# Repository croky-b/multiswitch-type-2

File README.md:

# multiswitch-type-2

/*================= TDB USM  ========================
   original code from bricodx : http://www.bricodx.fr/articles/9-arduino/16-commande-multifonctions/
   modified by croky_b for the Boat_Engine_system_MAXI
======================================================*/

not tested with 16 entry 

R1 180 ohm
R2 180 ohm

R3 2.2k ( for fotaba FC16)
R4 2.2k ( for futaba FC16)

R5 82k for old futaba F14 7 kanal ( if not used use SJ1)

OPTO PC817

Pinheader 
https://www.ebay.fr/itm/191203299649

switch
https://www.ebay.fr/itm/352543390865?hash=item5215393c91:g:xXUAAOSwkSde9JuG

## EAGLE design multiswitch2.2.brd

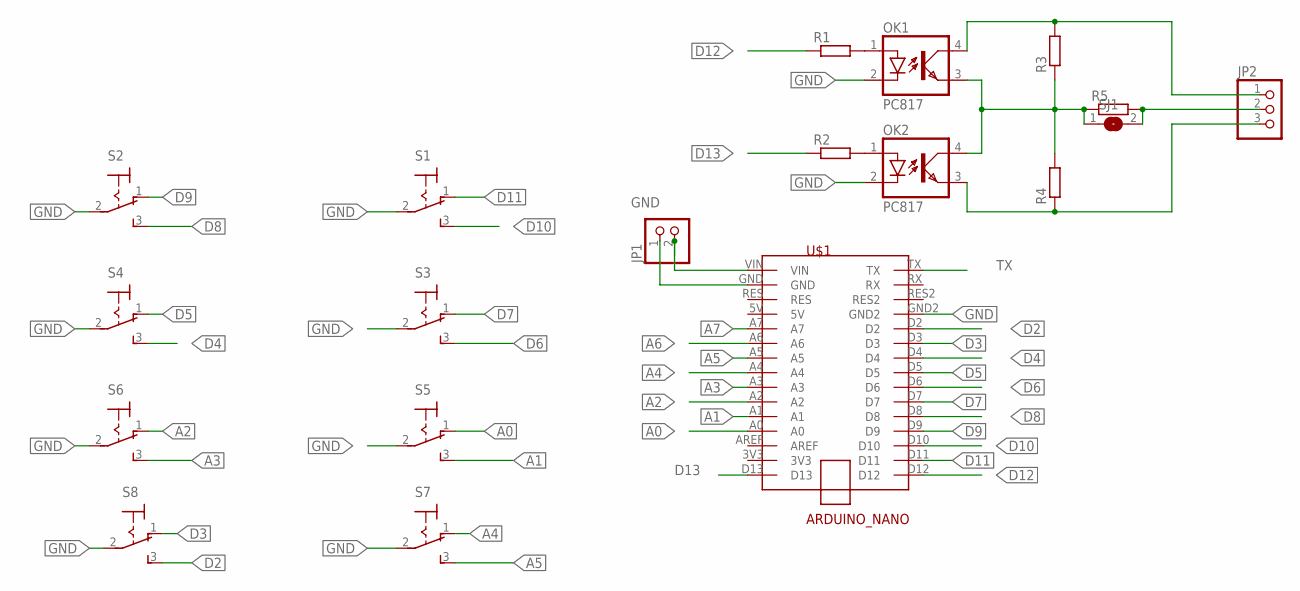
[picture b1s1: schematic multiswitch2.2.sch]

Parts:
JP1: PINHD-1X2; 1X02
JP2: PINHD-1X3; 1X03
OK1, OK2: PC817; DIL04
R1, R2, R3, R4, R5: R-EU_0204/7; 0204/7
S1, S2, S3, S4, S5, S6, S7, S8: M9040P
SJ1: SJ
U$1: ARDUINO_NANO; ARDUIN_NANO

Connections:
A0: S5.1 (O), U$1.A0
A1: S5.3 (S), U$1.A1
A2: S6.1 (O), U$1.A2
A3: S6.3 (S), U$1.A3
A4: S7.1 (O), U$1.A4
A5: S7.3 (S), U$1.A5
A6: U$1.A6
A7: U$1.A7
D2: S8.3 (S), U$1.D2
D3: S8.1 (O), U$1.D3
D4: S4.3 (S), U$1.D4
D5: S4.1 (O), U$1.D5
D6: S3.3 (S), U$1.D6
D7: S3.1 (O), U$1.D7
D8: S2.3 (S), U$1.D8
D9: S2.1 (O), U$1.D9
D10: S1.3 (S), U$1.D10
D11: S1.1 (O), U$1.D11
D12: R1.1, U$1.D12
D13: R2.1, U$1.D13
GND: JP1.1, OK1.2 (C), OK2.2 (C), S1.2, S2.2, S3.2, S4.2, S5.2, S6.2, S7.2, S8.2, U$1.GND, U$1.GND2
unnamed: OK1.1 (A), R1.2
unnamed: OK2.1 (A), R2.2
unnamed: JP2.1, OK1.4 (COL), R3.2
unnamed: OK1.3 (EMIT), OK2.4 (COL), R3.1, R4.2, R5.1, SJ1.1
unnamed: JP2.3, OK2.3 (EMIT), R4.1
unnamed: JP2.2, R5.2, SJ1.2
unnamed: JP1.2, U$1.VIN
TX: U$1.TX

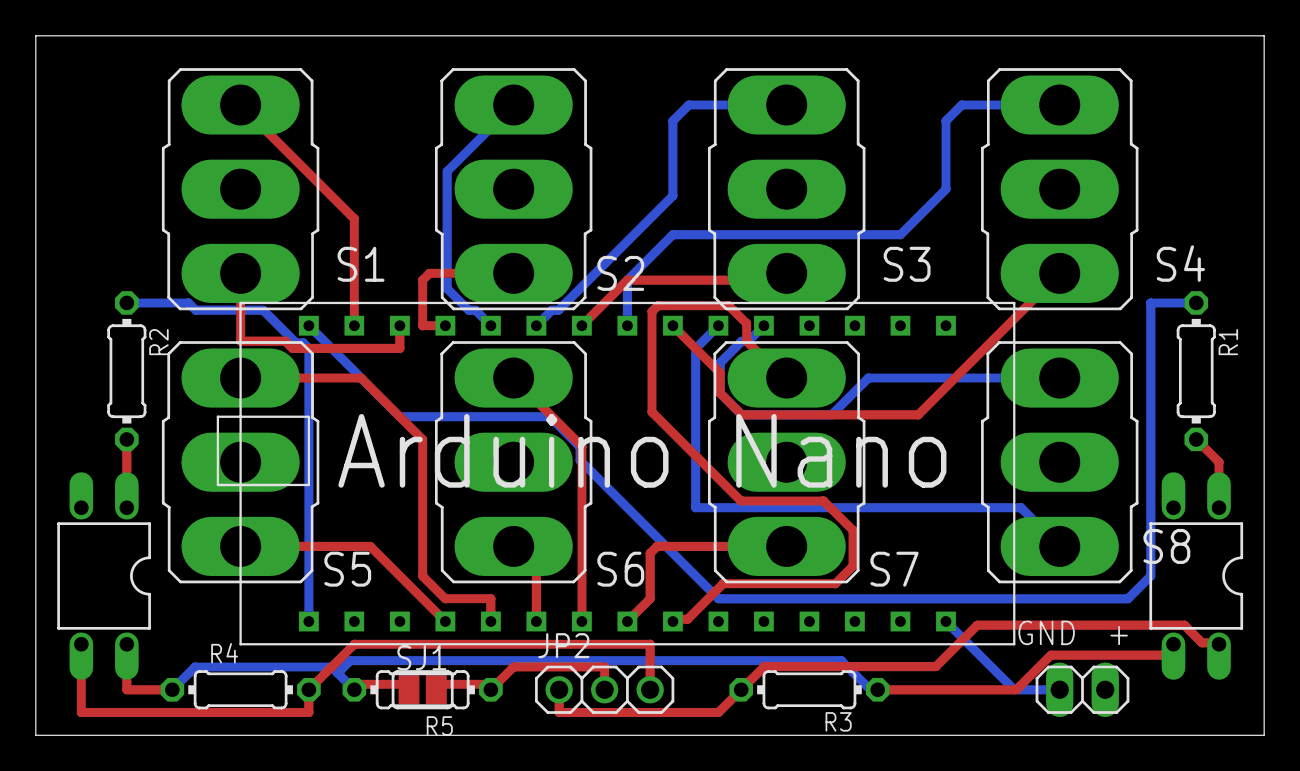
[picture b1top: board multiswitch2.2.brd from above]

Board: 2 copper layers, 68.6 x 39.0 mm, 19 parts (0 on the bottom side), 26 nets.
